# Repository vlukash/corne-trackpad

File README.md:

# Trackpad in a Keycap for Corne/CrKbd Keyboard

This is a Trackpad add-on for the [Corne](https://github.com/foostan/crkbd) keyboard.

This add-on consists of two main parts:
- an adapter PCB that goes between Elite-C and the main keyboard
- a connector PCB that links trackpad with the adapter

There are two different options available for the Trackpad sensor mount (connector PCB)
- on the 'H' button keycap via flex cable (Connector V1)
- no-flex mount directly on the connector PCB (Connector V2)

Both options compatible with the main adapter PCB, see photos below.

Schematics and PCB design included in this repository.
[Trackpad.c](https://github.com/vlukash/qmk_firmware/blob/master/keyboards/crkbd/keymaps/vlukash_trackpad_right/trackpad.c) reads the trackpad data and sends it to QMK.

Please find more information in my [blogpost](https://vlukash.com/2019/01/15/trackpad-in-keycap-corne-crkbd-keyboard/).

## Video
Turn on the subtitles option :)

https://www.youtube.com/watch?v=eY_9cieYMEQ

## Build Guide
https://github.com/vlukash/corne-trackpad/blob/master/build-guide.md

## Firmware
Corne keyboard uses [QMK](https://github.com/qmk/qmk_firmware) - an open-source keyboard firmware project.  
Please use [QMK guide](https://docs.qmk.fm/#/newbs_getting_started) to setup your local environment.  

The Trackpad add-on uses right-master configuration, and USB cable connects to the right keyboard with the trackpad.

Because of the adapter PCB, left and right keyboards have to be flashed with different firmware.

To build and flash the right keyboard (with the trackpad):
```
make crkbd:vlukash_trackpad_right:dfu
```
And the left part
```
make crkbd:vlukash_trackpad_left:dfu
```

[Here is a PR](https://github.com/qmk/qmk_firmware/pull/5925) that could be used as an example for creating your own Corne keymaps with the Trackpad add-on support.

## Photos
Trackpad sensor mounted directly on the connector PCB (Connector V2):

Trackpad sensor mounted on 'H' button keycap via flex cable (Connector V1):

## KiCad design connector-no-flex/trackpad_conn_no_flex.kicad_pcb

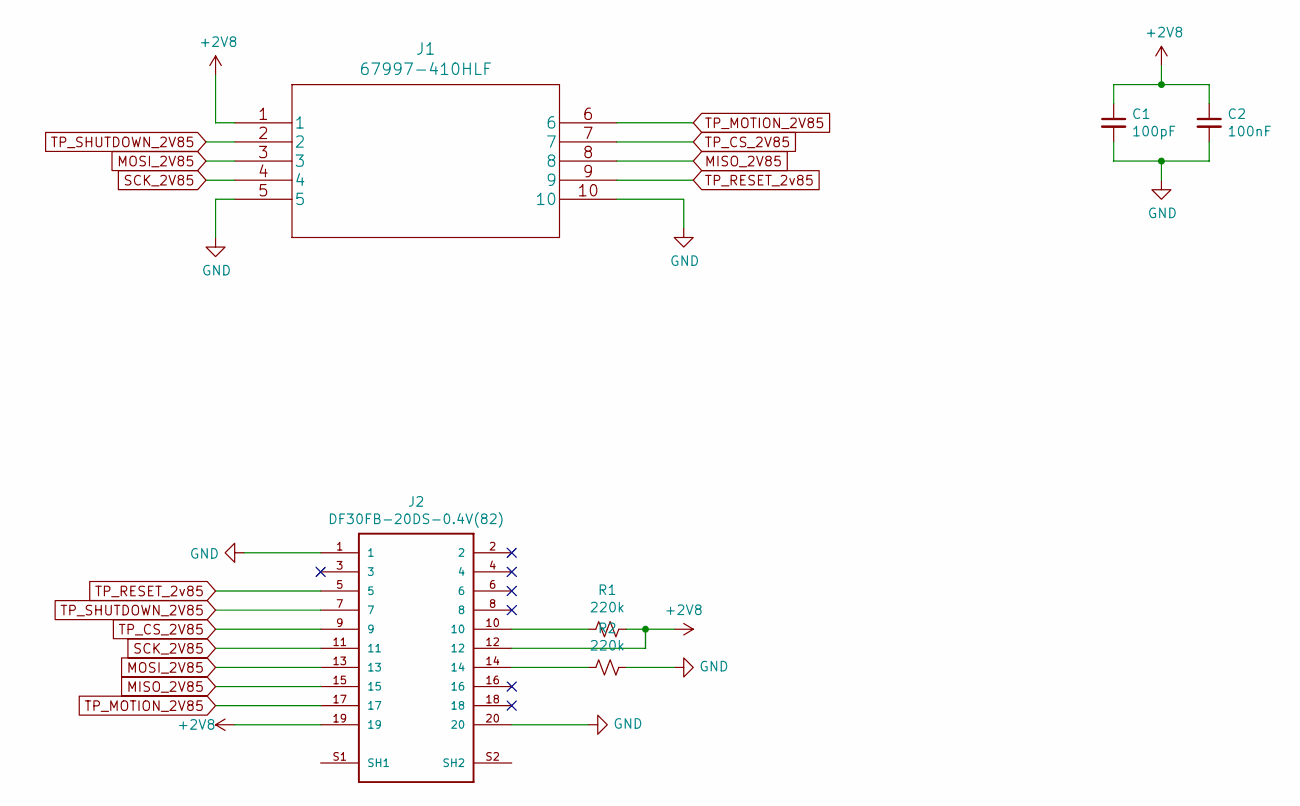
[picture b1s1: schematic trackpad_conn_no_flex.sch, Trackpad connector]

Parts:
C1: 100pF; C_0805_2012Metric
C2: 100nF; C_0805_2012Metric
J1: 67997-410HLF
J2: DF30FB-20DS-0.4V(82); HIROSE_DF30FB-20DS-0.4V(82)
R1, R2: 220k; R_0805_2012Metric

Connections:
+2V8: C1.1, C2.1, J1.1, J2.12, J2.19, R1.1
GND: C1.2, C2.2, J1.5, J1.10, J2.1, J2.20, R2.1
MISO_2V85: J1.8, J2.15
MOSI_2V85: J1.3, J2.13
unnamed: J2.10, R1.2
unnamed: J2.14, R2.2
SCK_2V85: J1.4, J2.11
TP_CS_2V85: J1.7, J2.9
TP_MOTION_2V85: J1.6, J2.17
TP_RESET_2v85: J1.9, J2.5
TP_SHUTDOWN_2V85: J1.2, J2.7

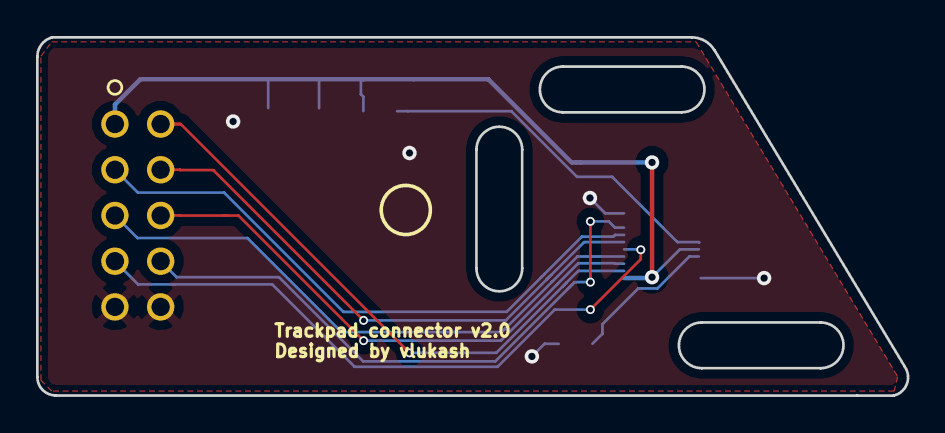
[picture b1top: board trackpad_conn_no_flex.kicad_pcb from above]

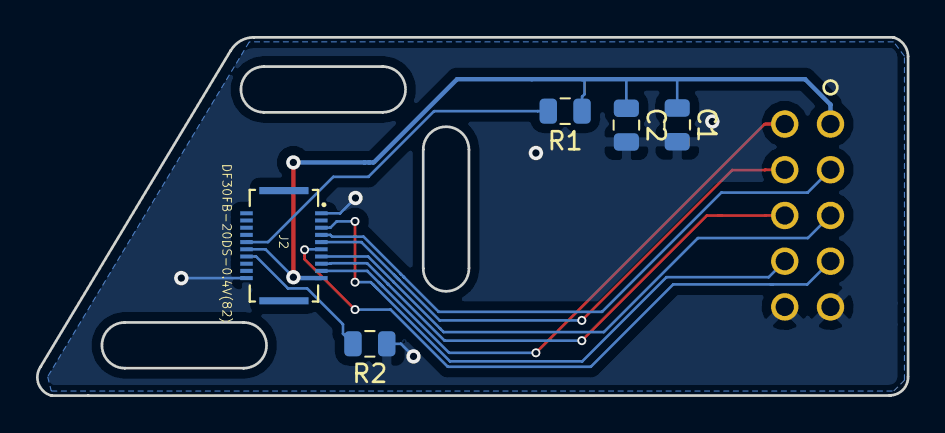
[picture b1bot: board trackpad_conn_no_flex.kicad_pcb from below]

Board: 2 copper layers, 48.4 x 19.9 mm, 6 parts (5 on the bottom side), 11 nets.

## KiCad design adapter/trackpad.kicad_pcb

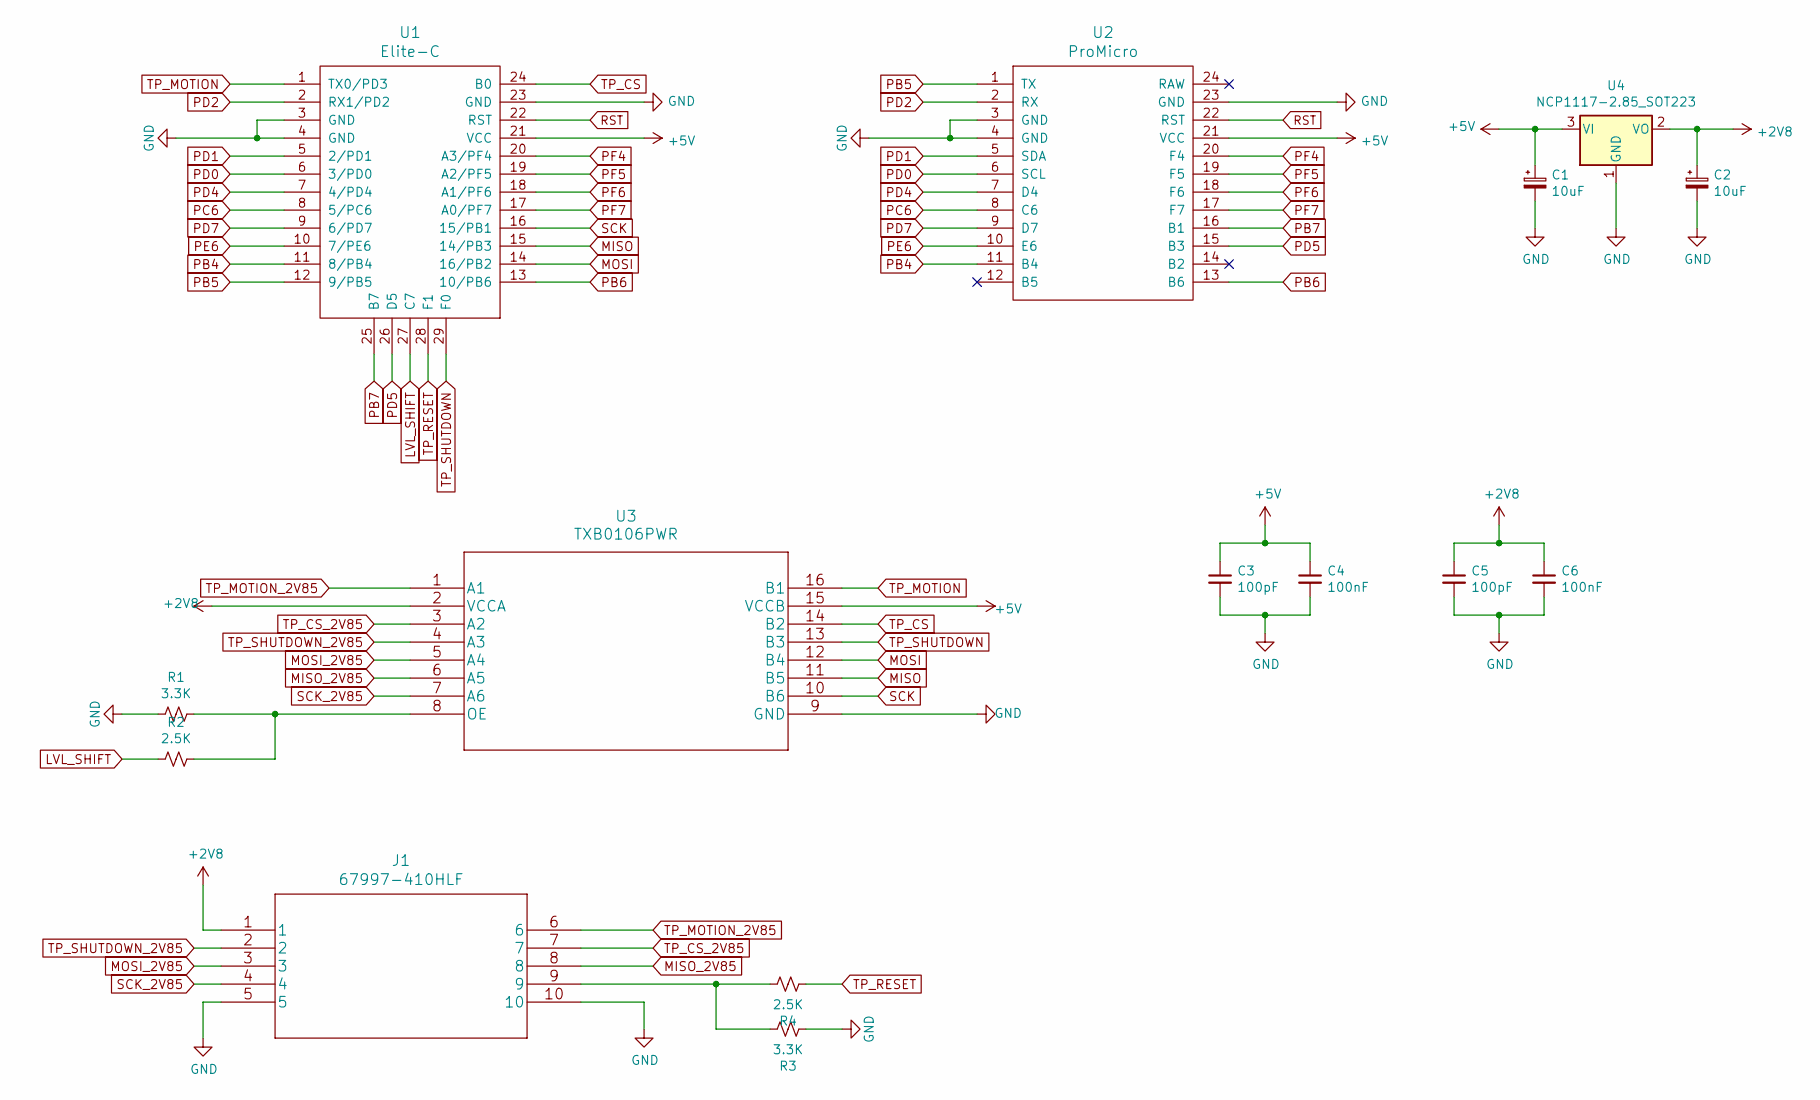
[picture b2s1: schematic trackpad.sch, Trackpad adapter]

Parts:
C1, C2: 10uF; CP_EIA-6032-15_Kemet-U
C3, C5: 100pF; C_0805_2012Metric
C4, C6: 100nF; C_0805_2012Metric
J1: 67997-410HLF
R1, R3: 3.3K; R_0805_2012Metric
R2, R4: 2.5K; R_0805_2012Metric
U1: Elite-C
U2: ProMicro; ArduinoProMicro
U3: TXB0106PWR
U4: NCP1117-2.85_SOT223; SOT-223-3_TabPin2

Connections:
+2V8: C2.1, C5.1, C6.1, J1.1, U3.2 (VCCA), U4.2 (VO)
+5V: C1.1, C3.1, C4.1, U1.21 (VCC), U2.21 (VCC), U3.15 (VCCB), U4.3 (VI)
GND: C1.2, C2.2, C3.2, C4.2, C5.2, C6.2, J1.5, J1.10, R1.2, R3.2, U1.3 (GND), U1.4 (GND), U1.23 (GND), U2.3 (GND), U2.4 (GND), U2.23 (GND), U3.9 (GND), U4.1 (GND)
LVL_SHIFT: R2.2, U1.27 (C7)
MISO: U1.15 (14/PB3), U3.11 (B5)
MISO_2V85: J1.8, U3.6 (A5)
MOSI: U1.14 (16/PB2), U3.12 (B4)
MOSI_2V85: J1.3, U3.5 (A4)
unnamed: J1.9, R3.1, R4.1
unnamed: R1.1, R2.1, U3.8 (OE)
PB4: U1.11 (8/PB4), U2.11 (B4)
PB5: U1.12 (9/PB5), U2.1 (TX)
PB6: U1.13 (10/PB6), U2.13 (B6)
PB7: U1.25 (B7), U2.16 (B1)
PC6: U1.8 (5/PC6), U2.8 (C6)
PD0: U1.6 (3/PD0), U2.6 (SCL)
PD1: U1.5 (2/PD1), U2.5 (SDA)
PD2: U1.2 (RX1/PD2), U2.2 (RX)
PD4: U1.7 (4/PD4), U2.7 (D4)
PD5: U1.26 (D5), U2.15 (B3)
PD7: U1.9 (6/PD7), U2.9 (D7)
PE6: U1.10 (7/PE6), U2.10 (E6)
PF4: U1.20 (A3/PF4), U2.20 (F4)
PF5: U1.19 (A2/PF5), U2.19 (F5)
PF6: U1.18 (A1/PF6), U2.18 (F6)
PF7: U1.17 (A0/PF7), U2.17 (F7)
RST: U1.22 (RST), U2.22 (RST)
SCK: U1.16 (15/PB1), U3.10 (B6)
SCK_2V85: J1.4, U3.7 (A6)
TP_CS: U1.24 (B0), U3.14 (B2)
TP_CS_2V85: J1.7, U3.3 (A2)
TP_MOTION: U1.1 (TX0/PD3), U3.16 (B1)
TP_MOTION_2V85: J1.6, U3.1 (A1)
TP_RESET: R4.2, U1.28 (F1)
TP_SHUTDOWN: U1.29 (F0), U3.13 (B3)
TP_SHUTDOWN_2V85: J1.2, U3.4 (A3)

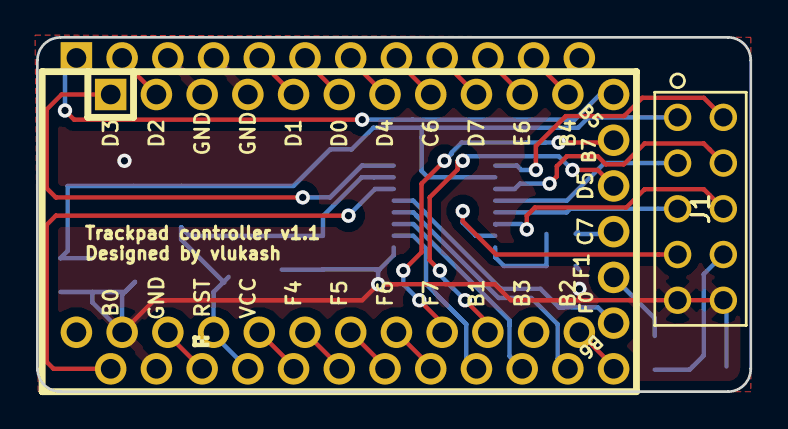
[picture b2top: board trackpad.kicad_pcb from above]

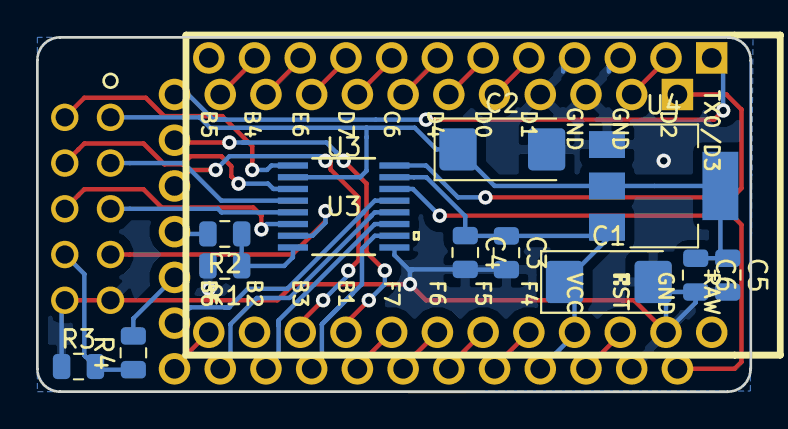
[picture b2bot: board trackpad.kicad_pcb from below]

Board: 2 copper layers, 39.6 x 19.7 mm, 15 parts (14 on the bottom side), 36 nets.

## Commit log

2019-01-17 Add trackpad schematics and PCB designs.
2019-01-22 Update readme file
2019-01-23 Add schematics in PDF format
2019-03-24 Update PCB length so it doesn't block USB-C connector.
2019-03-24 Add v2.0 connector. This version designed for direct trackpad mount on the PCB, instead of the keycap.
2019-03-31 Add trackpad build guide.
2019-05-19 Update readme file with trackpad build guide link.
2019-06-12 Add a Firmware section to the README file.

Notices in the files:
parts and their libraries:
Copyright 2016 Accelerated Designs. All rights reserved.
